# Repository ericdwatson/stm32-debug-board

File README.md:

# STM32 Debug Board

A custom STM32F446ZE development board (hardware revision V1.0) designed for embedded software development, hardware debugging and testing.

**Hardware status:** V1.0 successfully manufactured and functionally validated, including standalone operation at 180 MHz. No corrective PCB rework was required during the planned bench tests.

## Description

The intent behind this project was to generate a board with three commonly used STM32 programming/debugging interfaces and verify that all work correctly. I used an STM32F446ZE because I want to use this part on a separate project, so wanted to create a test board that verifies all debug interfaces work as expected, then select the ones I want to use for that and future boards.

The project includes the KiCad hardware design, manufacturing files, STM32CubeMX/STM32CubeIDE example firmware and a hardware and firmware validation report.

Designed using KiCad 10.0.3.

## Board Preview

### KiCad 3D Render - V1.0

### Manufactured PCB - V1.0

## Hardware Features

- STM32F446ZET6 microcontroller: ARM Cortex-M4 with FPU, 512 KB flash, 128 KB SRAM, up to 180 MHz.
- ARM 20-pin JTAG/SWD debug interface (J2).
- STDC14 debug interface with virtual COM port support (J3).
- Additional six-pin SWD/SWO connector (J4).
- USB-C 5 V power input (power only; no USB data), 500 mA fuse and 3.3 V linear regulator.
- 8 MHz external crystal oscillator.
- Power indicator and two active-low user LEDs.
- User pushbutton, hardware reset button and BOOT0 jumper.
- Two-layer, 75 × 75 mm PCB with ENIG finish.

## Debug Interfaces

| Connector | Interface | SWD | JTAG | SWO | UART / VCP |
| --- | --- | :---: | :---: | :---: | :---: |
| J2 | ARM 20-pin, 2.54 mm | Yes | Yes | Yes | — |
| J3 | STDC14, 1.27 mm | Yes | Yes | Yes | Yes |
| J4 | Six-pin, 2.54 mm | Yes | — | Yes | — |

All three SWD interfaces, both JTAG interfaces and all three SWO interfaces have been functionally tested. J3 also provides bidirectional USART3 communication through the STLINK-V3MINIE virtual COM port.

### Tested Debuggers

| Debugger | Target connector | Test results |
| --- | --- | --- |
| ST-LINK/V2-ISOL | J2 | SWD, JTAG, SWO and debugger reset passed |
| STLINK-V3MINIE | J3 | SWD, JTAG, SWO, debugger reset and VCP passed |
| ST-LINK/V2-ISOL | J4 | SWD, SWO and debugger reset passed |
| Third-party ST-LINK/V2-style probe | J4 | SWD programming and breakpoint debugging passed in STM32CubeIDE; STM32CubeProgrammer connection unsuccessful |

The genuine ST probes were used with their corresponding ribbon cables on J2 and J3. J4 was tested using individual wires. Tests were conducted during incremental firmware development; not every probe and system-clock combination was retested at 180 MHz.

### J4 — Six-pin SWD Connector

**Connection precautions:** Disconnect target and probe power before changing connections. Power the target from its own USB-C input. Verify connector orientation, pin 1 and the probe pinout before connecting. J4 pin 1 is the target's 3.3 V reference, not an input for a probe's power supply. Do not connect ST-LINK/V2 pin 19 or third-party probe power outputs to the powered target.

The following wiring was successfully tested with the ST-LINK/V2-ISOL:

| J4 pin | Target signal | ST-LINK/V2-ISOL pin |
| ---: | --- | ---: |
| 1 | 3.3 V reference / VAPP | 1 |
| 2 | GND | **20** |
| 3 | SWDIO | 7 |
| 4 | SWCLK | 9 |
| 5 | NRST | 15 |
| 6 | SWO | 13 |

**Important:** The isolated ST-LINK/V2 has a different pinout from the standard ST-LINK/V2. Pin 4 is not ground on the isolated model. Use pin 20 for ground in the wiring above. See ST's [UM1075 user manual](https://www.st.com/resource/en/user_manual/dm00026748.pdf), Tables 4 and 5, and the validation report for details.

### Third-party ST-LINK/V2-style Debugger

The following low-cost 10-pin debugger (purchased from Amazon) was also tested successfully with STM32CubeIDE over SWD.

With the target powered separately, only three wires were connected:

| Debugger pin (tested unit only) | J4 pin | Signal |
| ---: | ---: | --- |
| 2 | 4 | SWCLK |
| 4 | 3 | SWDIO |
| 6 | 2 | GND |

No power or reset wires were connected. SWO and debugger-controlled reset were not tested with this probe. Other visually similar probes may have different pinouts or firmware; verify the markings and documentation for your specific unit. Genuine ST probes are recommended for reproducibility.

## Example Firmware

The [STM32 Debug Board test application](software/stm32_debug_board_test/) is an STM32CubeMX-generated STM32CubeIDE project using STM32CubeF4 V1.28.3 and the HAL drivers. The final configuration uses the external 8 MHz crystal and PLL to run the MCU at 180 MHz.

The application demonstrates:

- Alternating user LEDs every 500 ms.
- USART3 startup message and a one-second heartbeat.
- UART character echo at 115200 baud, 8 data bits, no parity, one stop bit, no flow control.
- User pushbutton press and release messages with 20 ms debounce.
- SWO/ITM diagnostic messages once per second, using stimulus port 0.
- Hardware reset and standalone startup without a connected debugger.

### Clock Configuration

| Clock | Final frequency |
| --- | ---: |
| HSE crystal | 8 MHz |
| SYSCLK / HCLK | 180 MHz |
| APB1 peripheral clock | 45 MHz |
| APB2 peripheral clock | 90 MHz |
| PLLQ output | 45 MHz (unused for USB/SDIO) |

The main PLL uses M=4, N=180, P=2, Q=8 and R=2, with voltage Scale 1, OverDrive and five flash wait states. The earlier 16 MHz HSI and direct 8 MHz HSE firmware configurations remain available in the Git history.

### Debug Configurations

Three reusable STM32CubeIDE launch configurations are included in the firmware project:

| Launch file | Purpose |
| --- | --- |
| `stm32_debug_board_test.launch` | SWD programming and debugging |
| `stm32_debug_board_test_JTAG.launch` | JTAG programming and debugging |
| `stm32_debug_board_test_SWV.launch` | SWD with Serial Wire Viewer (SWV) trace |

The SWV configuration uses a 180 MHz core clock setting and a 1 MHz SWO clock limit. If the firmware clock is changed, update the SWV core clock setting accordingly.

## Getting Started

### Hardware and Firmware

1. With power disconnected, connect a suitable debugger to the appropriate target connector. The STLINK-V3MINIE on J3 is recommended for access to SWD, JTAG, SWO and UART/VCP.
2. Ensure the BOOT0 jumper is open for normal application startup. Power the target using a 5 V USB-C supply and connect the debugger to the host computer.
3. Open STM32CubeIDE and import the existing project from `software/stm32_debug_board_test/`.
4. Build the Debug configuration.
5. Select the appropriate launch configuration from **Run → Debug Configurations** and start debugging.
6. Resume execution from `main()`. The two user LEDs should alternate every 500 ms.

The [CubeMX configuration file](software/stm32_debug_board_test/stm32_debug_board_test.ioc) is included for further firmware development. Preserve the user-code sections if regenerating the code. No regeneration is necessary simply to build the supplied firmware.

### UART and SWO Diagnostics

For UART output, connect through J3 using the STLINK-V3MINIE and open its virtual COM port at 115200 baud (8N1, no flow control). The application reports its startup, sends a `Running...` heartbeat once per second, echoes individual characters and reports button events.

For SWO output, use the SWV launch configuration and open the **SWV ITM Data Console** in STM32CubeIDE. While halted at `main()`, enable ITM stimulus port 0 if necessary, start trace capture and resume execution. The console should display `SWO: Running...` once per second.

See the validation report for detailed test results and troubleshooting, including the CubeMX PLLQ divider workaround.

## Hardware and Firmware Validation

The V1.0 prototype successfully completed the planned functional bench tests on 12 November 2026.

| Test | Result |
| --- | --- |
| Power supply and 3.3 V rail (~3.29 V measured) | PASS |
| SWD on J2, J3 and J4 | PASS |
| JTAG on J2 and J3 | PASS |
| SWO on J2, J3 and J4 | PASS |
| Bidirectional UART via J3 | PASS |
| User LEDs, button and hardware reset | PASS |
| Internal 16 MHz HSI oscillator | PASS |
| External 8 MHz HSE crystal | PASS |
| 180 MHz PLL, OverDrive and clock register checks | PASS |
| Final application regression and repeated standalone cold starts | PASS |

Final standalone USB input current was approximately 60 mA at 180 MHz. No PCB design defects were identified during the planned tests and no corrective hardware rework was required.

These results represent functional prototype validation, not exhaustive peripheral testing or production qualification.

### Validation Report

The full report includes test evidence, debugger connection details, clock configurations, power measurements, limitations and lessons learned:

- [Hardware and Firmware Validation Report — Markdown](hardware/docs/validation-report/STM32_Debug_Board_V1.0_Validation_Report.md)
- [Hardware and Firmware Validation Report — PDF](hardware/docs/validation-report/STM32_Debug_Board_V1.0_Validation_Report.pdf)

## Repository Structure

```text
stm32-debug-board/
├── hardware/                    KiCad hardware project
│   ├── assets/                   Board images and debugger photographs
│   ├── docs/                     Schematic, BOM and validation documentation
│   │   ├── bom/
│   │   ├── pdf/
│   │   └── validation-report/
│   ├── libs/                     Project-specific KiCad libraries and 3D models
│   ├── datasheets/               Component documentation
│   └── manufacture/              PCB fabrication and assembly outputs
├── software/
│   └── stm32_debug_board_test/   STM32CubeMX / STM32CubeIDE project
└── README.md
```

## Hardware Documentation and Manufacturing

- [Schematic — PDF](hardware/docs/pdf/stm32_debug_board_v1_0.pdf)
- [Bill of materials — CSV](hardware/docs/bom/stm32_debug_board.csv)
- [KiCad hardware project](hardware/)
- [Manufacturing files](hardware/manufacture/)

V1.0 was manufactured by JLCPCB as a two-layer, 75 × 75 mm PCB with ENIG finish. Five boards were ordered: two with top-side SMD assembly and three bare PCBs. The through-hole components were fitted manually for testing.

The manufacturing directory contains the V1.0 fabrication and assembly outputs, including Gerbers, drill files, BOM and component placement files.

## Version History

| Version | Date | Author | Description |
| --- | --- | --- | --- |
| 0.1 | 30/10/2026 | E. Watson | Initial version for review. |
| 0.2 | 30/10/2026 | E. Watson | Minor updates after review including footprint fixes. |
| 1.0 | 31/10/2026 | E. Watson | Folder portability issues fixed. Version added to PCB. |

V1.0 hardware and firmware validation completed on 12/11/2026. The PCB revision remains unchanged following testing.

## Licence

## Licence

Copyright (c) 2026 E. Watson.

This project is intended for public use and is released under the following licences:

| Project Content | Licence |
|---|---|
| Original hardware design and manufacturing files | [CERN-OHL-P-2.0](LICENSES/CERN-OHL-P-2.0.txt) |
| Original application firmware | [MIT](LICENSES/MIT.txt) |
| Original documentation and photographs | [CC BY 4.0](LICENSES/CC-BY-4.0.txt) |
| Third-party libraries, drivers and 3D models | Their respective licences |

The original hardware and application software may be used, modified and redistributed for personal or commercial purposes, subject to the applicable licence conditions.

Third-party components retain their original copyright notices and licensing terms.

For further information, see:

- [Project Licensing](LICENSE.md)
- [Third-Party Notices](THIRD_PARTY_NOTICES.md)
- [Full Licence Texts](LICENSES/)

This project is provided without warranty, subject to the terms of the applicable licences.

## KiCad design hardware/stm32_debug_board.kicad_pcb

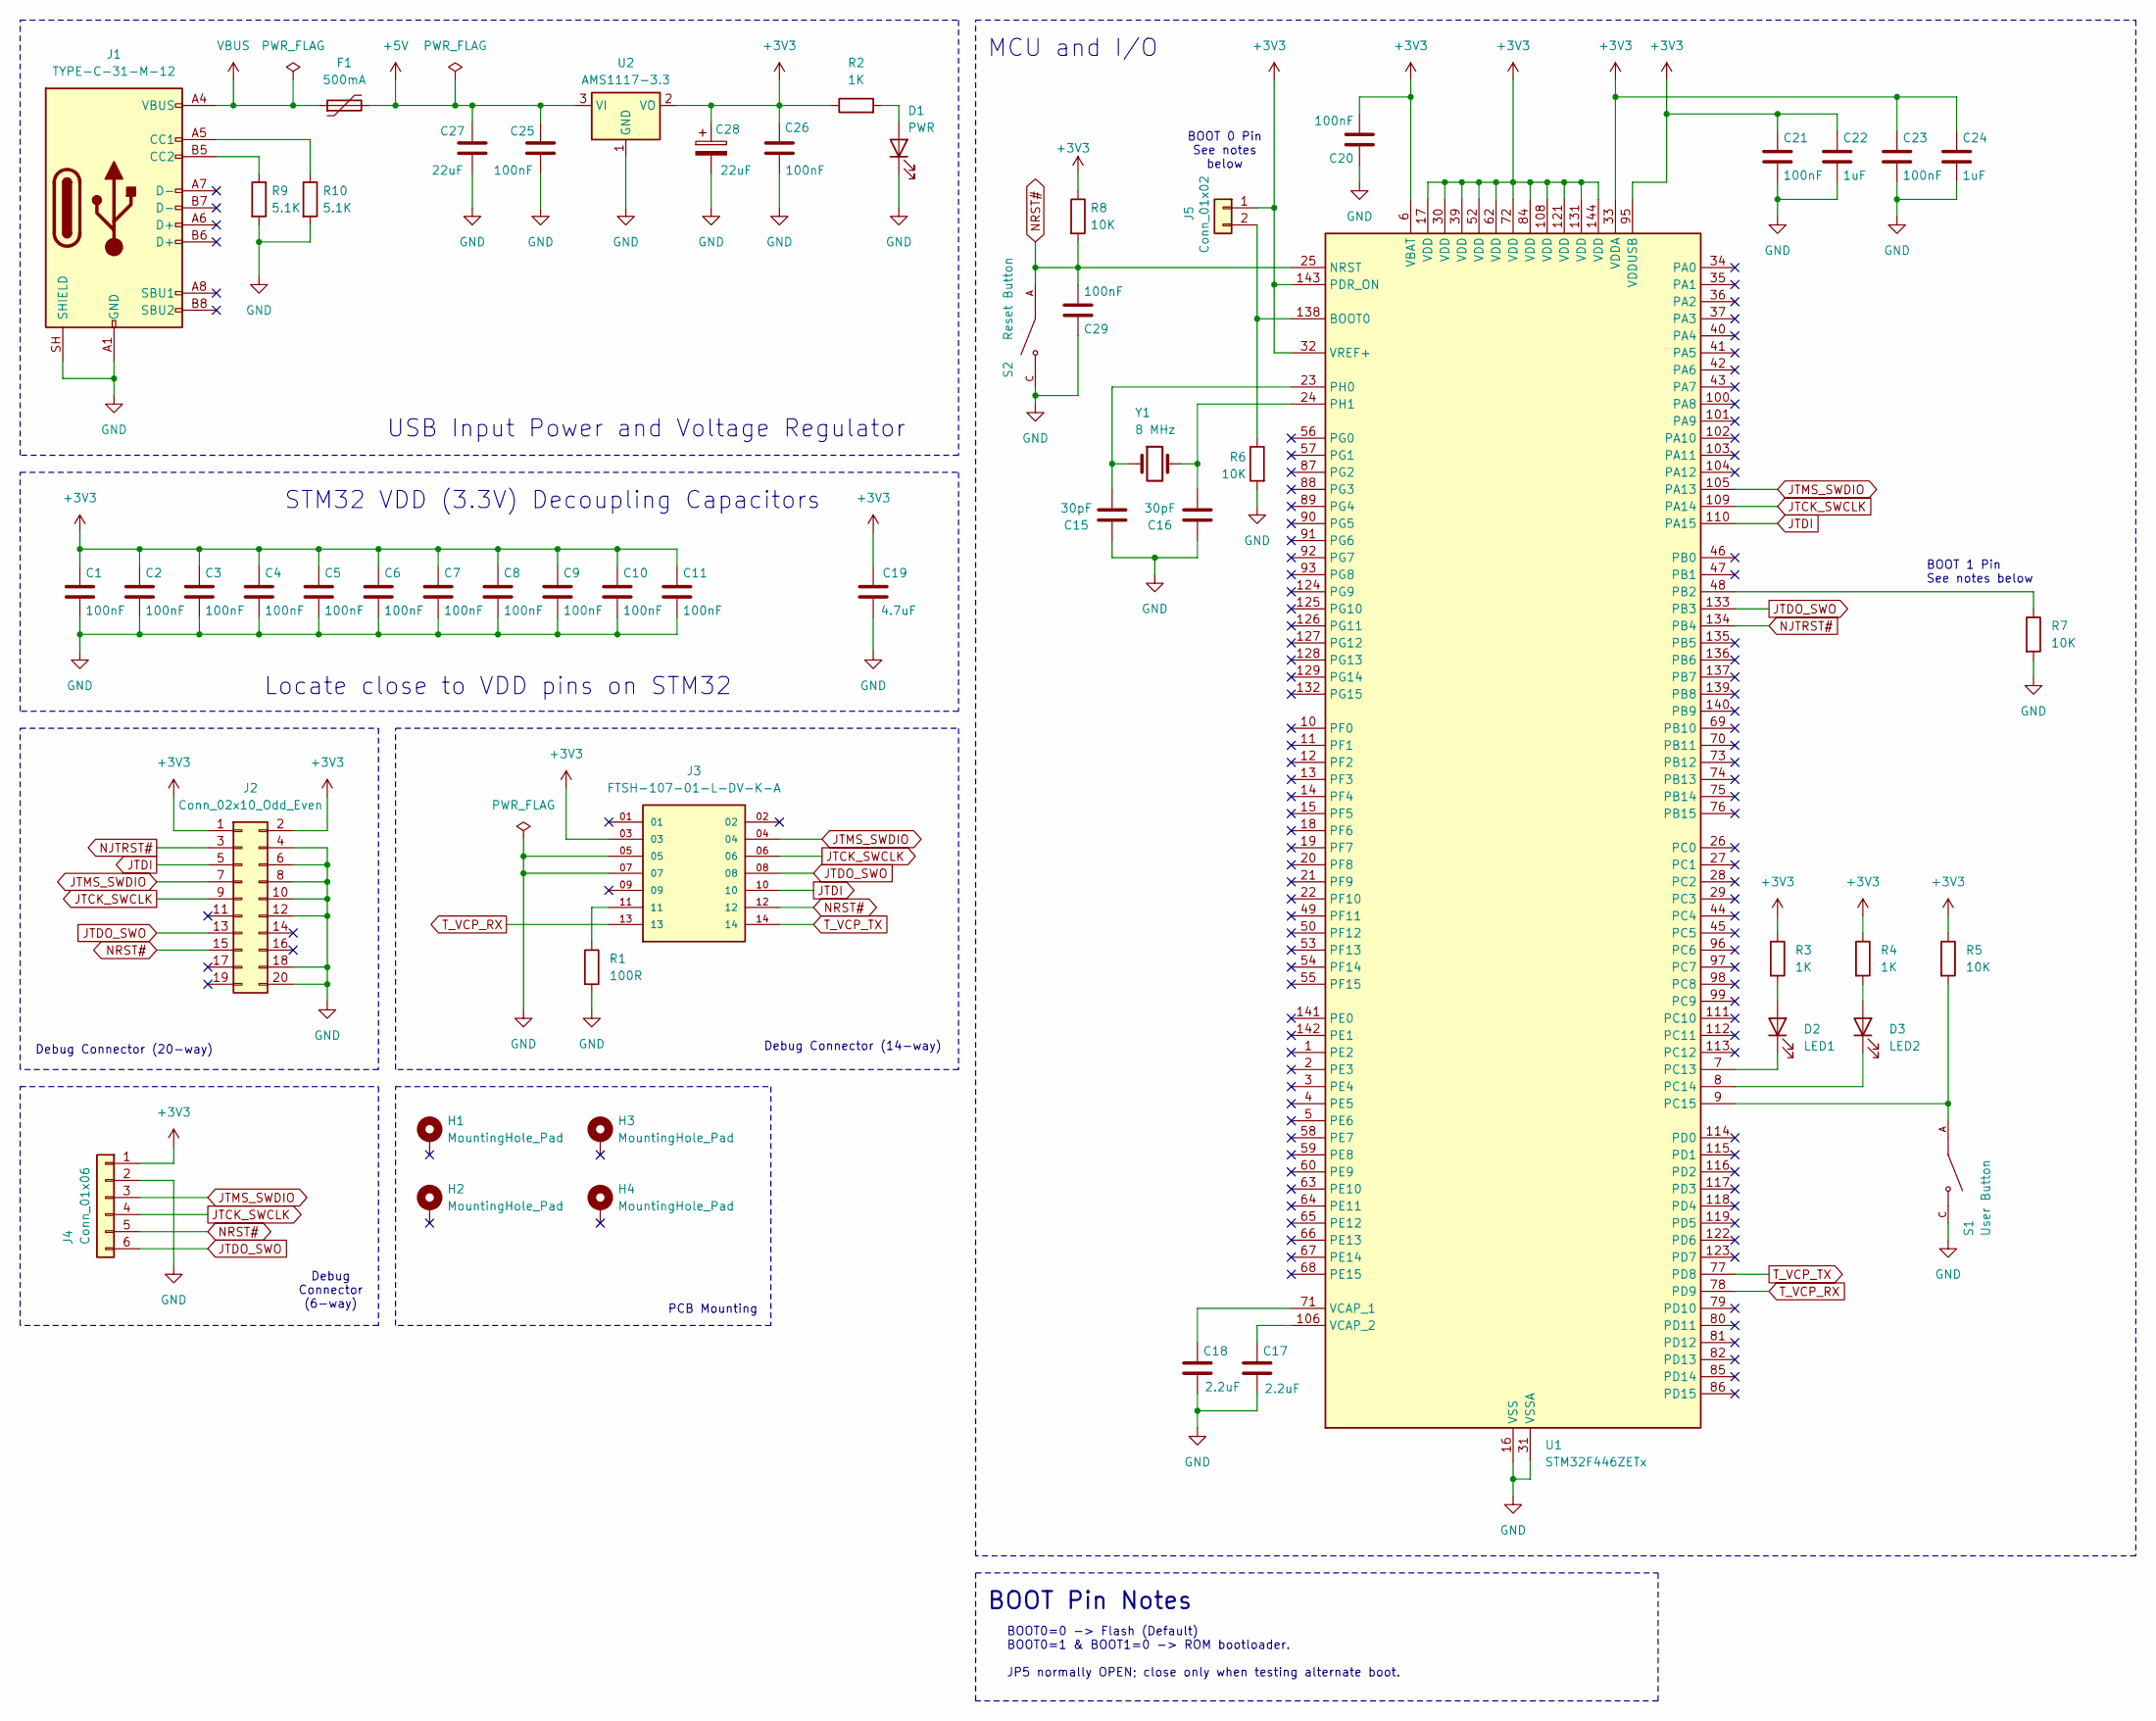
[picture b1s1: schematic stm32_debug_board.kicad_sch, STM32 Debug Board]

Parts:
C1, C2, C3, C4, C5, C6, C7, C8, C9, C10, C11, C20, C21, C23, C25, C26, C29: 100nF; C_0805_2012Metric; LCSC C49678
C15, C16: 30pF; C_0603_1608Metric; MPN 0603CG300J500NT; LCSC C1658
C17, C18: 2.2uF; C_0805_2012Metric; LCSC C377773
C19: 4.7uF; C_0805_2012Metric; MPN CL21A475KAQNNNE; LCSC C1779
C22, C24: 1uF; C_0805_2012Metric; LCSC C28323
C27: 22uF; C_0805_2012Metric; MPN CL21A226MAQNNNE; LCSC C45783
C28: 22uF; CP_EIA-3528-21_Kemet-B; MPN TAJB226K010RNJ; LCSC C7198
D1: PWR; LED_0805_2012Metric; MPN KT-0805Y; LCSC C2296
D2: LED1; LED_0805_2012Metric; MPN KT-0805Y; LCSC C2296
D3: LED2; LED_0805_2012Metric; MPN KT-0805Y; LCSC C2296
F1: 500mA; Fuse_1206_3216Metric; MPN 500mA/24V; LCSC C2984676
H1, H2, H3, H4: MountingHole_Pad; MountingHole_3.2mm_M3_Pad
J1: TYPE-C-31-M-12; USB_C_Receptacle_HRO_TYPE-C-31-M-12; MPN TYPE-C-31-M-12; LCSC C165948
J2: Conn_02x10_Odd_Even; IDC-Header_2x10_P2.54mm_Vertical; MPN TST-110-01-G-D; Farnell 2667391
J3: FTSH-107-01-L-DV-K-A; SAMTEC_FTSH-107-01-L-DV-K-A; PARTREV H; LCSC C5563894
J4: Conn_01x06; PinHeader_1x06_P2.54mm_Vertical; MPN TSW-106-07-G-S; Farnell 2856716
J5: Conn_01x02; PinHeader_1x02_P2.54mm_Vertical
R1: 100R; R_0805_2012Metric; MPN 0805W8F1000T5E; LCSC C17408
R2, R3, R4: 1K; R_0805_2012Metric; MPN 0805W8F1001T5E; LCSC C17513
R5, R6, R7, R8: 10K; R_0805_2012Metric; MPN 0805W8F1002T5E; LCSC C17414
R9, R10: 5.1K; R_0805_2012Metric; MPN 0805W8F5101T5E; LCSC C27834
S1: User Button; SW_TS-1187A-B-A-B; PARTREV A0; LCSC C318884
S2: Reset Button; SW_TS-1187A-B-A-B; PARTREV A0; LCSC C318884
U1: STM32F446ZETx; LQFP-144_20x20mm_P0.5mm; LCSC C1337227
U2: AMS1117-3.3; SOT-223-3_TabPin2; LCSC C6186
Y1: 8 MHz; Crystal_SMD_5032-2Pin_5.0x3.2mm; MPN X50328MSB2GI; LCSC C115962

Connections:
+3V3: C1.1, C2.1, C3.1, C4.1, C5.1, C6.1, C7.1, C8.1, C9.1, C10.1, C11.1, C19.1, C20.2, C21.1, C22.1, C23.1, C24.1, C26.2, C28.1, J2.1, J2.2, J3.03, J4.1, J5.1, R2.1, R3.1, R4.1, R5.1, R8.1, U1.6 (VBAT), U1.17 (VDD), U1.30 (VDD), U1.32 (VREF+), U1.33 (VDDA), U1.39 (VDD), U1.52 (VDD), U1.62 (VDD), U1.72 (VDD), U1.84 (VDD), U1.95 (VDDUSB), U1.108 (VDD), U1.121 (VDD), U1.131 (VDD), U1.143 (PDR_ON), U1.144 (VDD), U2.2 (VO)
+5V: C25.2, C27.2, F1.2, U2.3 (VI)
GND: C1.2, C2.2, C3.2, C4.2, C5.2, C6.2, C7.2, C8.2, C9.2, C10.2, C11.2, C15.1, C16.1, C17.2, C18.2, C19.2, C20.1, C21.2, C22.2, C23.2, C24.2, C25.1, C26.1, C27.1, C28.2, C29.1, D1.1 (K), J1.A1 (GND), J1.A12 (GND), J1.B1 (GND), J1.B12 (GND), J1.SH (SHIELD), J2.4, J2.6, J2.8, J2.10, J2.12, J2.18, J2.20, J3.05, J3.07, J4.2, R1.2, R6.2, R7.2, R9.2, R10.2, S1.C, S1.D, S2.C, S2.D, U1.16 (VSS), U1.31 (VSSA), U1.38 (VSS), U1.51 (VSS), U1.61 (VSS), U1.83 (VSS), U1.94 (VSS), U1.107 (VSS), U1.120 (VSS), U1.130 (VSS), U2.1 (GND)
JTCK_SWCLK: J2.9, J3.06, J4.4, U1.109 (PA14)
JTDI: J2.5, J3.10, U1.110 (PA15)
JTDO_SWO: J2.13, J3.08, J4.6, U1.133 (PB3)
JTMS_SWDIO: J2.7, J3.04, J4.3, U1.105 (PA13)
NJTRST#: J2.3, U1.134 (PB4)
NRST#: C29.2, J2.15, J3.12, J4.5, R8.2, S2.A, S2.B, U1.25 (NRST)
unnamed: D1.2 (A), R2.2
unnamed: D2.2 (A), R3.2
unnamed: D2.1 (K), U1.7 (PC13)
unnamed: D3.2 (A), R4.2
unnamed: D3.1 (K), U1.8 (PC14)
unnamed: J1.A5 (CC1), R10.1
unnamed: J1.B5 (CC2), R9.1
unnamed: J3.11, R1.1
unnamed: J5.2, R6.1, U1.138 (BOOT0)
unnamed: R7.1, U1.48 (PB2)
unnamed: R5.2, S1.A, S1.B, U1.9 (PC15)
unnamed: C15.2, U1.23 (PH0), Y1.1
unnamed: C16.2, U1.24 (PH1), Y1.2
unnamed: C18.1, U1.71 (VCAP_1)
unnamed: C17.1, U1.106 (VCAP_2)
T_VCP_RX: J3.13, U1.78 (PD9)
T_VCP_TX: J3.14, U1.77 (PD8)
VBUS: F1.1, J1.A4 (VBUS), J1.A9 (VBUS), J1.B4 (VBUS), J1.B9 (VBUS)

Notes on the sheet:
MCU and I/O
Debug Connector (20-way)
BOOT0=0 -> Flash (Default) BOOT0=1 & BOOT1=0 -> ROM bootloader. JP5 normally OPEN; close only when testing alternate boot.
Locate close to VDD pins on STM32
PCB Mounting
Debug Connector (6-way)
USB Input Power and Voltage Regulator
BOOT 1 Pin See notes below
BOOT 0 Pin See notes below
Debug Connector (14-way)
STM32 VDD (3.3V) Decoupling Capacitors
BOOT Pin Notes

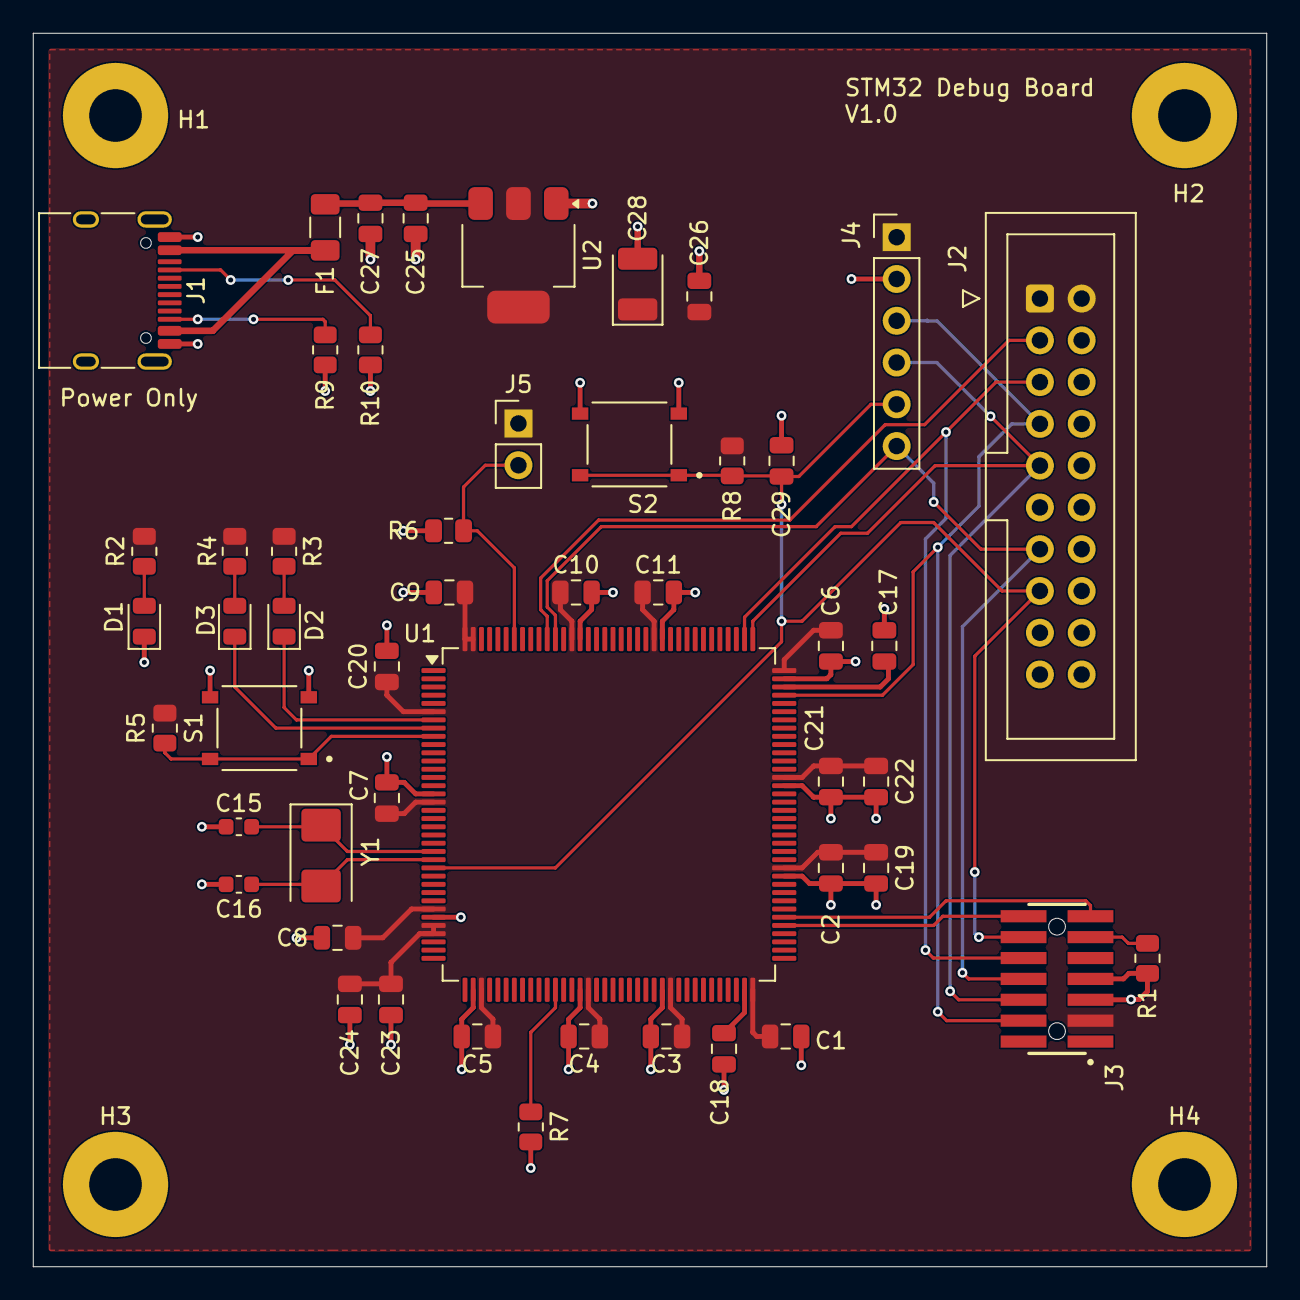
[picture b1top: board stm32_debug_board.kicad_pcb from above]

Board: 2 copper layers, 75.0 x 75.0 mm, 54 parts (0 on the bottom side), 27 nets.

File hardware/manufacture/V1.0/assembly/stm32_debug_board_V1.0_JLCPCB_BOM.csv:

Comment,Designator,Footprint,LCSC Part #
100nF,"C1,C2,C3,C4,C5,C6,C7,C8,C9,C10,C11,C20,C21,C23,C25,C26,C29",C_0805_2012Metric,C49678
30pF,"C15,C16",C_0603_1608Metric,C1658
2.2uF,"C17,C18",C_0805_2012Metric,C377773
4.7uF,C19,C_0805_2012Metric,C1779
1uF,"C22,C24",C_0805_2012Metric,C28323
22uF,C27,C_0805_2012Metric,C45783
22uF,C28,CP_EIA-3528-21_Kemet-B,C7198
LED 0805,"D1,D2,D3",LED_0805_2012Metric,C2296
500mA,F1,Fuse_1206_3216Metric,C2984676
TYPE-C-31-M-12,J1,USB_C_Receptacle_HRO_TYPE-C-31-M-12,C165948
FTSH-107-01-L-DV-K-A,J3,SAMTEC_FTSH-107-01-L-DV-K-A,C5563894
100R,R1,R_0805_2012Metric,C17408
1K,"R2,R3,R4",R_0805_2012Metric,C17513
10K,"R5,R6,R7,R8",R_0805_2012Metric,C17414
5.1K,"R9,R10",R_0805_2012Metric,C27834
Momentary switch,"S1,S2",SW_TS-1187A-B-A-B,C318884
STM32F446ZETx,U1,LQFP-144_20x20mm_P0.5mm,C1337227
AMS1117-3.3,U2,SOT-223-3_TabPin2,C6186
8 MHz,Y1,Crystal_SMD_5032-2Pin_5.0x3.2mm,C115962

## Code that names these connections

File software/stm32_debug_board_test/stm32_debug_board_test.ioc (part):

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Mcu.Name=STM32F446Z(C-E)Tx
Mcu.Package=LQFP144
Mcu.UserName=STM32F446ZETx
PA13.Mode=Trace_Asynchronous_SW
PA13.Signal=SYS_JTMS-SWDIO
PA14.Mode=Trace_Asynchronous_SW
PA14.Signal=SYS_JTCK-SWCLK
PB3.Mode=Trace_Asynchronous_SW
PB3.Signal=SYS_JTDO-SWO
PC13.GPIOParameters=PinState,GPIO_Label
PC13.GPIO_Label=LED1
PC13.PinState=GPIO_PIN_SET
PC13.Signal=GPIO_Output
PC14-OSC32_IN.GPIOParameters=PinState,GPIO_Label
PC14-OSC32_IN.GPIO_Label=LED2
PC14-OSC32_IN.PinState=GPIO_PIN_SET
PC14-OSC32_IN.Signal=GPIO_Output
PC15-OSC32_OUT.GPIOParameters=GPIO_Label
PC15-OSC32_OUT.GPIO_Label=USER_BUTTON
PC15-OSC32_OUT.Signal=GPIO_Input
PD8.GPIOParameters=GPIO_Speed,GPIO_Label
PD8.GPIO_Label=T_VCP_TX
PD8.GPIO_Speed=GPIO_SPEED_FREQ_LOW
PD8.Mode=Asynchronous
PD8.Signal=USART3_TX
PD9.GPIOParameters=GPIO_Speed,GPIO_Label
PD9.GPIO_Label=T_VCP_RX
PD9.GPIO_Speed=GPIO_SPEED_FREQ_LOW
PD9.Mode=Asynchronous
PD9.Signal=USART3_RX
PH0-OSC_IN.Mode=HSE-External-Oscillator
PH0-OSC_IN.Signal=RCC_OSC_IN
PH1-OSC_OUT.Mode=HSE-External-Oscillator
PH1-OSC_OUT.Signal=RCC_OSC_OUT
RCC.HSE_VALUE=8000000
RCC.SYSCLKFreq_VALUE=180000000
RCC.SYSCLKSource=RCC_SYSCLKSOURCE_PLLCLK
board=custom

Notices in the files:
hardware/stm32_debug_board.kicad_pcb:
SPDX-License-Identifier: CERN-OHL-P-2.0
